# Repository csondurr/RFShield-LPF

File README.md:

# RFShield LPF

<p align="center">
  <strong>Python-assisted, PCB-aware 108–500 MHz / 50 Ω seventh-order RF low-pass filter design.</strong>
</p>

## Türkçe proje özeti

**RFShield LPF**, 50 Ω RF sinyal zincirlerinde **108 MHz ile 500 MHz** arasındaki işaretleri düşük kayıpla geçirmek ve daha yüksek frekans bileşenlerini bastırmak amacıyla geliştirilmiş, iki katmanlı, yedinci dereceden bir alçak geçiren filtre PCB projesidir. Tasarım; ayrık L/C değer optimizasyonu, parasitik etkileri içeren PCB-farkındalıklı analitik model, 50 Ω mikroşerit sentezi, Monte Carlo tolerans analizi, KiCad dosya üretimi, DRC doğrulaması ve üretim çıktılarının hazırlanması aşamalarını kapsar.

Bu çalışma bir **mühendislik prototipi** olarak yayımlanmaktadır. Analitik sonuçlar ve KiCad doğrulaması güçlü bir tasarım temeli sağlar; ancak fiziksel üretim sonrası VNA ölçümü, tam dalga elektromanyetik analiz ve hedef RF güç seviyesinde doğrulama yapılmadan seri üretim, maksimum güç veya mevzuat uyumluluğu iddiasında bulunulmaz.

---

## 1. Repository integrity and revision status

The public product name is **RFShield LPF**. Some checked-in files still use the original internal engineering identifier `CEM_RF_LPF_500_FINAL` and the historical revision label `REV_B`. Those identifiers are retained here for traceability and do not change the intended product name.

### Important status distinction

The repository currently contains an earlier engineering snapshot whose checked-in [`drc_summary.json`](drc_summary.json) reports:

```text
20 DRC warnings
0 unconnected items
```

All 20 warnings are of the same class: `via_dangling`. They were generated because the RF-route stitching vias were connected to the bottom ground plane but did not yet have a continuous top-copper connection.

A later **REV_C** production run corrected this by adding continuous F.Cu ground guard rails that electrically join the via fence on both copper layers. That run completed with:

```text
Found 0 violations
Found 0 unconnected items
```

Therefore:

- the RF topology and selected component values are the final intended design;
- the checked-in REV_B DRC report is historical evidence of the issue that was found;
- the corrected REV_C geometry is the manufacturing target;
- the current repository snapshot should not be treated as the final fabrication master until the corrected REV_C board source and its new DRC report are committed together.

This distinction is documented explicitly to avoid presenting a historical DRC report as if it were the final validated source.

---

## 2. Design objectives

| Parameter | Target |
|---|---:|
| Intended passband | 108–500 MHz |
| Reference impedance | 50 Ω |
| Filter class | Low-pass |
| Filter order | 7 |
| Network form | Symmetrical series-L / shunt-C ladder |
| PCB layer count | 2 |
| Nominal finished thickness | 1.60 mm |
| Nominal copper thickness | 35 µm |
| Nominal substrate | FR-4 |
| Nominal relative permittivity | 4.30 |
| Nominal loss tangent | 0.018 |
| Nominal dielectric height to ground | 1.53 mm |
| Input/output connector | 50 Ω SMA |
| Maximum analytical passband insertion-loss gate | 1.00 dB |
| Minimum analytical passband return-loss gate | 12.0 dB |
| Minimum analytical attenuation at 1 GHz | 25.0 dB |
| Minimum Monte Carlo pass gate | 95% |

The design is intended for use as a prototype output or interstage low-pass network in sub-500 MHz RF systems. Typical applications may include:

- harmonic suppression after a low-VHF/UHF RF stage;
- receiver front-end or laboratory filtering;
- SDR test chains;
- RF measurement fixtures;
- educational study of practical lumped-element filters and PCB parasitics.

It is not tied to one transmitter, one output power, one national emission mask, or one certified product.

---

## 3. Electrical topology

RFShield LPF uses a symmetrical seventh-order ladder:

```text
J1 ─ L1 ─●─ L3 ─●─ L5 ─●─ L7 ─ J2
         │      │      │
         C2     C4     C6
         │      │      │
        GND    GND    GND
```

Net sequence:

```text
RF_IN → L1 → N1 → L3 → N2 → L5 → N3 → L7 → RF_OUT
             │          │          │
             C2         C4         C6
             │          │          │
            GND        GND        GND
```

The symmetry reduces unnecessary input/output asymmetry and simplifies model verification.

### Selected values

| References | Quantity | Selected value | Tolerance used in analysis | Intended component family |
|---|---:|---:|---:|---|
| L1, L7 | 2 | 8.2 nH | ±5% | Coilcraft 0603HP high-Q RF inductor |
| L3, L5 | 2 | 15 nH | ±5% | Coilcraft 0603HP high-Q RF inductor |
| C2, C6 | 2 | 4.3 pF | ±0.1 pF | KYOCERA AVX 600S high-Q C0G/NP0 |
| C4 | 1 | 4.3 pF | ±0.1 pF | KYOCERA AVX 600S high-Q C0G/NP0 |
| J1, J2 | 2 | 50 Ω SMA | — | Amphenol RF 132134-10 family |

Intended example manufacturer part numbers:

| Function | Example MPN |
|---|---|
| 8.2 nH inductor | `0603HP-8N2XJRW` |
| 15 nH inductor | `0603HP-15NXJRW` |
| 4.3 pF capacitor | `600S4R3BT250XT4K` |
| SMA connector | `132134-10` |

Substitution must be based on RF characteristics, not only nominal value and package size. Inductor Q, self-resonant frequency, capacitor ESR/ESL, dielectric technology, pad geometry and connector launch geometry directly affect the upper passband and first stopband octave.

---

## 4. Why a seventh-order Chebyshev-style ladder was used

A higher-order ladder provides a steeper transition than a simple third- or fifth-order network while remaining practical with discrete components. The design began from a classical low-pass prototype approach and was then optimized using real candidate values and a PCB-aware model rather than relying on one ideal calculation followed by simple E-series rounding.

For an ideal low-pass prototype, series inductors and shunt capacitors can be scaled using:

```text
Lk = gk · Z0 / ωc
Ck = gk / (Z0 · ωc)
```

where:

- `gk` is the normalized prototype coefficient;
- `Z0` is the 50 Ω system impedance;
- `ωc` is the chosen angular cutoff frequency.

In a real PCB, the final values cannot be chosen from ideal equations alone because the transmission-line sections, component pads, vias, connector launches and finite component Q modify the response. RFShield LPF therefore performs a second-stage discrete optimization with these effects included.

---

## 5. Discrete component optimization

The engineering automation evaluates a finite candidate space rather than choosing the nearest values once.

Candidate sets:

```text
Outer inductors: 8.2, 9.1, 10, 11, 12 nH
Inner inductors: 15, 16, 18, 22, 24 nH
Outer capacitors: 4.3, 4.7, 5.1, 5.6, 6.2 pF
Center capacitor: 4.3, 4.7, 5.1, 5.6, 6.2 pF
```

Total combinations:

```text
5 × 5 × 5 × 5 = 625 candidate networks
```

Each candidate is evaluated from approximately 10 MHz to 2 GHz. The score penalizes:

- passband insertion loss;
- return loss falling below the acceptance gate;
- insufficient attenuation at 1 GHz;
- excessive passband ripple.

The best-performing candidate is selected automatically and the top 20 candidates are preserved in [`optimization_top20.json`](optimization_top20.json) for engineering traceability.

---

## 6. PCB-aware analytical model

The analysis cascades ABCD matrices for the individual network elements and converts the complete two-port network to S-parameters in a 50 Ω reference system.

### Series element matrix

```text
[ 1  Z ]
[ 0  1 ]
```

### Shunt element matrix

```text
[ 1  0 ]
[ Y  1 ]
```

### Transmission-line matrix

```text
[ cosh(γl)      Z0 sinh(γl) ]
[ sinh(γl)/Z0   cosh(γl)    ]
```

The complete matrix is the ordered product of connector, line, series-L, shunt-C and interconnect matrices.

### Included non-ideal effects

- frequency-dependent transmission-line electrical length;
- approximate conductor and dielectric loss;
- inductor finite Q;
- inductor parasitic capacitance estimated from self-resonant frequency;
- capacitor ESR;
- capacitor ESL;
- shunt-via inductance;
- dual-via ground return;
- finite shunt-stub length;
- connector series resistance and inductance;
- interstage microstrip lengths;
- real discrete candidate values.

### Effects not fully represented

- full 3D connector fields;
- solder fillets and assembly geometry;
- copper roughness tied to a specific laminate;
- vendor Touchstone models for every part;
- enclosure and cable coupling;
- radiation and higher-order mode effects;
- power-dependent heating and saturation;
- exact board-house etch and dielectric distributions.

The analytical model is therefore a strong design-screening tool, but it is not a substitute for full-wave EM simulation or calibrated measurement.

---

## 7. Predicted RF performance

The selected values produced the following PCB-aware analytical results:

| Metric | Predicted result |
|---|---:|
| Worst-case insertion loss in 108–500 MHz | **0.408 dB** |
| Worst-case return loss in 108–500 MHz | **23.370 dB** |
| Attenuation at 1 GHz | **30.837 dB** |
| S21 at 108 MHz | **−0.167 dB** |
| S21 at 500 MHz | **−0.409 dB** |
| S11 at 500 MHz | **−36.024 dB** |
| Predicted passband ripple | **0.242 dB** |

Machine-readable results are stored in [`design_summary.json`](design_summary.json).

### Interpretation

- The predicted passband loss is below the 1 dB engineering gate.
- The predicted return loss has significant margin above the 12 dB gate.
- The 1 GHz attenuation exceeds the 25 dB gate.
- These are model outputs, not measured VNA results.

No measured insertion-loss, return-loss, group-delay, power-handling or harmonic-compliance claim is made in this release.

---

## 8. Monte Carlo tolerance analysis

The selected design was evaluated with **400 deterministic, seeded Monte Carlo runs**.

Random seed:

```text
20260729
```

Tolerance assumptions:

- inductors: ±5%, represented as a normal distribution with the limit at approximately 3σ;
- capacitors: ±0.1 pF, represented in the same manner.

A run passes only when all three conditions are met:

```text
Worst passband IL ≤ 1.00 dB
Worst passband RL ≥ 12.0 dB
Attenuation at 1 GHz ≥ 25.0 dB
```

Reported model statistics:

| Metric | Result |
|---|---:|
| Monte Carlo runs | 400 |
| Passing runs | 100% |
| 95th-percentile passband IL | 0.415 dB |
| 5th-percentile passband RL | 22.161 dB |
| 5th-percentile attenuation at 1 GHz | 30.098 dB |

This result does not include every manufacturing variable. In particular, laminate Er variation, dielectric thickness tolerance, copper thickness, etch bias, connector spread and complete package-model uncertainty are not all randomized. The result must not be interpreted as a guaranteed production yield.

---

## 9. Stack-up and controlled impedance

Nominal two-layer stack-up:

```text
Top solder mask
F.Cu: 35 µm copper — RF components and signal routing
FR-4: Er = 4.30, tanδ = 0.018, nominal dielectric height = 1.53 mm
B.Cu: 35 µm copper — RF ground reference
Bottom solder mask
Nominal finished thickness: 1.60 mm
```

The microstrip width is solved with a Hammerstad-style quasi-static approximation.

| Parameter | Calculated value |
|---|---:|
| Target characteristic impedance | 50.000 Ω |
| Solved trace width | 2.9995 mm |
| Routed nominal trace width | 3.000 mm |
| Effective relative permittivity | 3.2683 |
| Calculated impedance at solved width | 50.000 Ω |

### Critical manufacturing warning

“1.6 mm FR-4” is not a complete controlled-impedance specification. Different fabricators may use different core/prepreg constructions, resin content, copper roughness and actual dielectric thickness.

Before ordering an impedance-controlled lot:

1. obtain the board house's actual stack-up;
2. confirm the dielectric height from F.Cu to B.Cu;
3. update Er, loss tangent and copper thickness;
4. recalculate the required trace width;
5. regenerate the PCB;
6. rerun DRC;
7. request an impedance coupon where available.

A 3.0 mm trace is appropriate only for the nominal stack-up used in this model. It is not a universal 50 Ω width.

---

## 10. PCB layout architecture

Nominal board dimensions:

```text
74 mm × 50 mm
```

### 10.1 RF signal path

The main RF route is kept linear and symmetrical. The nominal 50 Ω sections use a 3.0 mm microstrip width. Narrow necks are limited to locations where 0603 pad geometry requires a transition.

### 10.2 Ground reference

The bottom copper is intended as a continuous RF ground reference. A continuous reference plane minimizes loop area, lowers return-path inductance and makes the microstrip impedance definition physically meaningful.

### 10.3 Shunt-capacitor return paths

Each shunt capacitor requires a short and low-inductance path to ground. Dual local ground vias are used so that the shunt branches remain effective near the upper passband and into the stopband.

A long shared ground bus would add parasitic inductance, detune the ladder and reduce stopband attenuation. The layout avoids that architecture.

### 10.4 SMA launches

The SMA launches include nearby ground connections and stitching vias. The goal is to provide a short transition from the connector ground tabs to the bottom reference plane and to reduce connector-launch inductance.

The exact connector drawing must be checked against the purchased Amphenol part before fabrication. Similar-looking vertical SMA connectors are not footprint-compatible by default.

### 10.5 Via fence

The RF route is bordered by a ground via fence with an approximate 5 mm pitch. In the corrected REV_C geometry, front-copper guard rails connect the via fence on F.Cu while the bottom plane connects the same vias on B.Cu.

This change serves two purposes:

- it removes KiCad `via_dangling` warnings;
- it creates a physically continuous two-layer ground structure rather than a decorative set of vias connected on only one copper layer.

### 10.6 Local footprints

The project includes custom footprint sources:

- [`RF_0603.kicad_mod`](RF_0603.kicad_mod)
- [`SMA_AMPHENOL_132134_10.kicad_mod`](SMA_AMPHENOL_132134_10.kicad_mod)

The [`fp-lib-table`](fp-lib-table) expects a project-local library called `CUSTOM.pretty`. For a clean local checkout, place the two `.kicad_mod` files inside:

```text
CUSTOM.pretty/
```

so that the structure becomes:

```text
RFShield-LPF/
├── CEM_RF_LPF_500_FINAL.kicad_pcb
├── CEM_RF_LPF_500_FINAL.kicad_pro
├── fp-lib-table
└── CUSTOM.pretty/
    ├── RF_0603.kicad_mod
    └── SMA_AMPHENOL_132134_10.kicad_mod
```

The footprints embedded in the board allow the PCB to open, but restoring the intended local-library structure is recommended for future edits and reproducibility.

---

## 11. KiCad design files

| File | Purpose |
|---|---|
| [`CEM_RF_LPF_500_FINAL.kicad_pcb`](CEM_RF_LPF_500_FINAL.kicad_pcb) | Main PCB layout and embedded footprint geometry |
| [`CEM_RF_LPF_500_FINAL.kicad_pro`](CEM_RF_LPF_500_FINAL.kicad_pro) | KiCad project settings and net classes |
| [`CEM_RF_LPF_500_FINAL.kicad_prl`](CEM_RF_LPF_500_FINAL.kicad_prl) | KiCad local UI/session state; not required for fabrication |
| [`fp-lib-table`](fp-lib-table) | Project-local footprint library mapping |
| [`RF_0603.kicad_mod`](RF_0603.kicad_mod) | Custom RF 0603 land pattern |
| [`SMA_AMPHENOL_132134_10.kicad_mod`](SMA_AMPHENOL_132134_10.kicad_mod) | Custom SMA connector footprint |

The `.kicad_prl` file is machine/session specific and is normally excluded from a clean source repository. It is kept in the current snapshot only because it was included in the uploaded engineering package.

---

## 12. Reports and traceability files

| File | Description |
|---|---|
| [`design_summary.json`](design_summary.json) | Selected values, analytical metrics, Monte Carlo statistics and nominal stack-up |
| [`optimization_top20.json`](optimization_top20.json) | Ranked top 20 component combinations from the 625-candidate search |
| [`drc_report.json`](drc_report.json) | Historical KiCad 9.0.7 REV_B DRC report containing 20 `via_dangling` warnings |
| [`drc_summary.json`](drc_summary.json) | Compact summary of the historical REV_B DRC execution |

The report files are intended to make the design decision auditable instead of presenting only a final layout with no engineering history.

---

## 13. Opening the project

Recommended environment:

- Windows 10 or Windows 11;
- KiCad 9.0.7 or a compatible KiCad 9 release.

Procedure:

1. clone or download the repository;
2. create a `CUSTOM.pretty` folder in the repository root;
3. move the two `.kicad_mod` files into `CUSTOM.pretty`;
4. open `CEM_RF_LPF_500_FINAL.kicad_pro`;
5. open PCB Editor;
6. inspect the board stack-up, design rules, footprints and net classes;
7. refill or regenerate copper only when intentionally modifying the design;
8. run DRC locally before exporting any fabrication files.

Command-line DRC example:

```powershell
& "C:\Program Files\KiCad\9.0\bin\kicad-cli.exe" pcb drc `
  --output .\drc_report_new.json `
  --format json `
  --severity-all `
  --exit-code-violations `
  .\CEM_RF_LPF_500_FINAL.kicad_pcb
```

Do not assume that the historical checked-in report describes a modified local board. Always regenerate the report from the exact board revision intended for fabrication.

---

## 14. Intended automated production pipeline

The project was developed through a Python-driven engineering pipeline with the following sequence:

1. define RF and PCB requirements;
2. solve the nominal 50 Ω microstrip width;
3. validate board and component-placement constraints;
4. evaluate 625 discrete L/C candidate networks;
5. select the best candidate using PCB-aware metrics;
6. run 400 Monte Carlo tolerance trials;
7. enforce RF acceptance gates;
8. generate the KiCad PCB and project files;
9. generate custom project-local footprints;
10. generate analytical reports;
11. call KiCad CLI DRC;
12. require zero violations and zero unconnected items for release;
13. export Gerbers;
14. export PTH and NPTH drill files;
15. export drill maps;
16. export CSV component positions;
17. verify expected fabrication outputs;
18. create a production ZIP.

The current repository snapshot contains the generated design and reports, but it does not yet include the full Python automation source or the final REV_C fabrication archive. For complete reproducibility, those files should be versioned in a future repository cleanup.

---

## 15. Expected fabrication outputs

A complete release package should contain at minimum:

### Gerbers

- F.Cu;
- B.Cu;
- F.Paste;
- F.Silkscreen;
- B.Silkscreen;
- F.Mask;
- B.Mask;
- Edge.Cuts.

### Drill and assembly

- plated-through-hole Excellon file;
- non-plated-through-hole Excellon file;
- drill map;
- component position CSV;
- bill of materials;
- stack-up and impedance note;
- DRC report from the released source revision.

Gerber export example for KiCad 9:

```powershell
& "C:\Program Files\KiCad\9.0\bin\kicad-cli.exe" pcb export gerbers `
  --output .\fabrication\gerbers `
  --layers F.Cu,B.Cu,F.Paste,F.Silkscreen,B.Silkscreen,F.Mask,B.Mask,Edge.Cuts `
  .\CEM_RF_LPF_500_FINAL.kicad_pcb
```

Drill export example:

```powershell
& "C:\Program Files\KiCad\9.0\bin\kicad-cli.exe" pcb export drill `
  --output .\fabrication\drill `
  --format excellon `
  --excellon-units mm `
  --generate-map `
  --map-format pdf `
  --excellon-separate-th `
  .\CEM_RF_LPF_500_FINAL.kicad_pcb
```

---

## 16. Manufacturing checklist

Before ordering the PCB:

- use the corrected REV_C source, not the historical REV_B snapshot;
- confirm DRC is 0 violations and 0 unconnected items;
- verify every Gerber in an independent viewer;
- verify board dimensions and units;
- verify plated and non-plated drill separation;
- confirm the exact board-house stack-up;
- recalculate the 50 Ω width for that stack-up;
- confirm the exact SMA connector mechanical drawing;
- confirm 0603 component land patterns;
- verify solder-mask openings;
- verify via drill and annular-ring capability;
- verify copper-to-edge clearance;
- verify the BOM and current component availability;
- verify inductor Q and SRF for the full operating range;
- verify capacitor technology is C0G/NP0 or equivalent RF grade;
- order a small prototype quantity first;
- request impedance control or an impedance coupon where practical.

A DRC-clean board can still be electrically unsuitable at RF. Manufacturing review must include return-current paths, connector launches, trace impedance and parasitic behavior—not only geometric rule compliance.

---

## 17. Prototype assembly guidance

Recommended assembly sequence:

1. inspect the bare PCB for shorts, damaged mask and incorrect drill registration;
2. install the three shunt capacitors;
3. install the four series inductors;
4. install the SMA connectors with complete ground-tab soldering;
5. clean flux residues appropriate to the assembly process;
6. verify continuity from each ground pad and via to SMA ground;
7. verify there is no DC short from RF input to ground;
8. verify there is no DC short from RF output to ground;
9. inspect component alignment under magnification.

Because the component values are very small, excess solder, lifted parts, long solder fillets and incorrect component technology may noticeably shift the response.

---

## 18. VNA validation plan

Recommended first measurement:

1. warm up the VNA according to the instrument procedure;
2. use high-quality 50 Ω cables and minimize adapters;
3. perform SOLT calibration at the cable ends or use an appropriate fixture calibration;
4. sweep at least 10 MHz to 2 GHz;
5. record S11, S21, S12 and S22;
6. save Touchstone data;
7. compare measured S21 with the analytical response;
8. inspect passband loss, return loss, cutoff shift and first stopband resonance;
9. repeat on a second assembled PCB;
10. document the exact board stack-up and component lot.

Recommended plots:

- S21 magnitude from 10 MHz to 2 GHz;
- S11 and S22 magnitude;
- passband-only S21 zoom from 108 MHz to 500 MHz;
- group delay in the passband;
- measured-versus-modeled overlay.

Possible causes of model/measurement mismatch:

- actual Er or dielectric thickness differs from nominal;
- component Q/SRF differs from the simplified model;
- connector launch parasitics;
- incorrect or substitute components;
- via inductance and ground-return geometry;
- solder and pad parasitics;
- calibration-plane error;
- cable or adapter repeatability.

---

## 19. Power-path validation

Small-signal VNA data is not sufficient to establish a power rating.

For transmitter or PA use, perform a controlled power test with:

- a rated 50 Ω load;
- directional couplers;
- suitable attenuators;
- a spectrum analyzer or power meter;
- thermal monitoring;
- appropriate shielding and RF safety precautions.

Validate:

- insertion loss at operating power;
- harmonic attenuation;
- inductor current and temperature;
- capacitor RF voltage stress;
- connector heating;
- solder-joint heating;
- response drift with temperature;
- behavior under load mismatch.

No maximum RF power is claimed by this repository.

---

## 20. Known limitations

- The checked-in source snapshot is the historical REV_B package, not the corrected REV_C manufacturing master.
- The checked-in DRC report contains 20 `via_dangling` warnings.
- The final REV_C 0/0 DRC report is not yet committed.
- Physical VNA data is not yet published.
- Full-wave 2.5D/3D EM results are not yet published.
- The nominal FR-4 stack-up is not tied to one fabricator.
- The model uses engineering approximations for line and component parasitics.
- Vendor S-parameter files are not included.
- Maximum RF power has not been established.
- Thermal behavior has not been measured.
- Regulatory harmonic-emission compliance is not claimed.
- The filter has not been co-simulated with a specific PA output impedance.
- The current root-level footprint placement should be reorganized into `CUSTOM.pretty`.
- The complete automation source and production ZIP are not included in the present repository snapshot.

---

## 21. Engineering roadmap

Planned next steps:

- commit the corrected REV_C KiCad source;
- replace the historical DRC report with a revision-matched 0/0 report while preserving REV_B history in a separate folder;
- restore `CUSTOM.pretty` directory structure;
- add the full Python automation source;
- add BOM and component lifecycle information;
- add generated Gerbers and drills as a tagged release asset;
- perform ADS Momentum, Sonnet, CST or equivalent EM extraction;
- import vendor S-parameter models;
- manufacture at least two prototypes;
- publish calibrated VNA Touchstone files;
- correlate analytical and measured responses;
- evaluate power handling and thermal rise;
- optimize against a specific board-house stack-up;
- add automated repository validation and release checks.

---

## 22. Safety and regulatory notice

RF hardware can cause interference, equipment damage, burns and unlawful emissions when used incorrectly. The builder and operator are responsible for:

- complying with local spectrum regulations;
- using legal frequencies and power levels;
- using properly rated loads, cables, attenuators and instruments;
- preventing exposure to hazardous RF levels;
- ensuring that a transmitter system satisfies applicable harmonic and spurious-emission requirements.

This repository is provided as an engineering and educational project, not as regulatory certification.

---

## 23. Project metadata

| Field | Value |
|---|---|
| Public name | RFShield LPF |
| Internal engineering identifier | CEM_RF_LPF_500_FINAL |
| Intended final hardware revision | REV_C |
| Frequency range | 108–500 MHz |
| System impedance | 50 Ω |
| Filter order | 7 |
| PCB layers | 2 |
| Primary EDA tool | KiCad 9.0.7 |
| Analysis environment | Python, NumPy-based numerical model |
| Author | Cem Sondur |
| Project year | 2026 |

---

## 24. License and use

Unless a separate license file is added, all project files remain copyright of **Cem Sondur**.

No warranty is provided. Anyone fabricating, modifying or operating the design is responsible for independent review, measurement, safety and regulatory compliance.

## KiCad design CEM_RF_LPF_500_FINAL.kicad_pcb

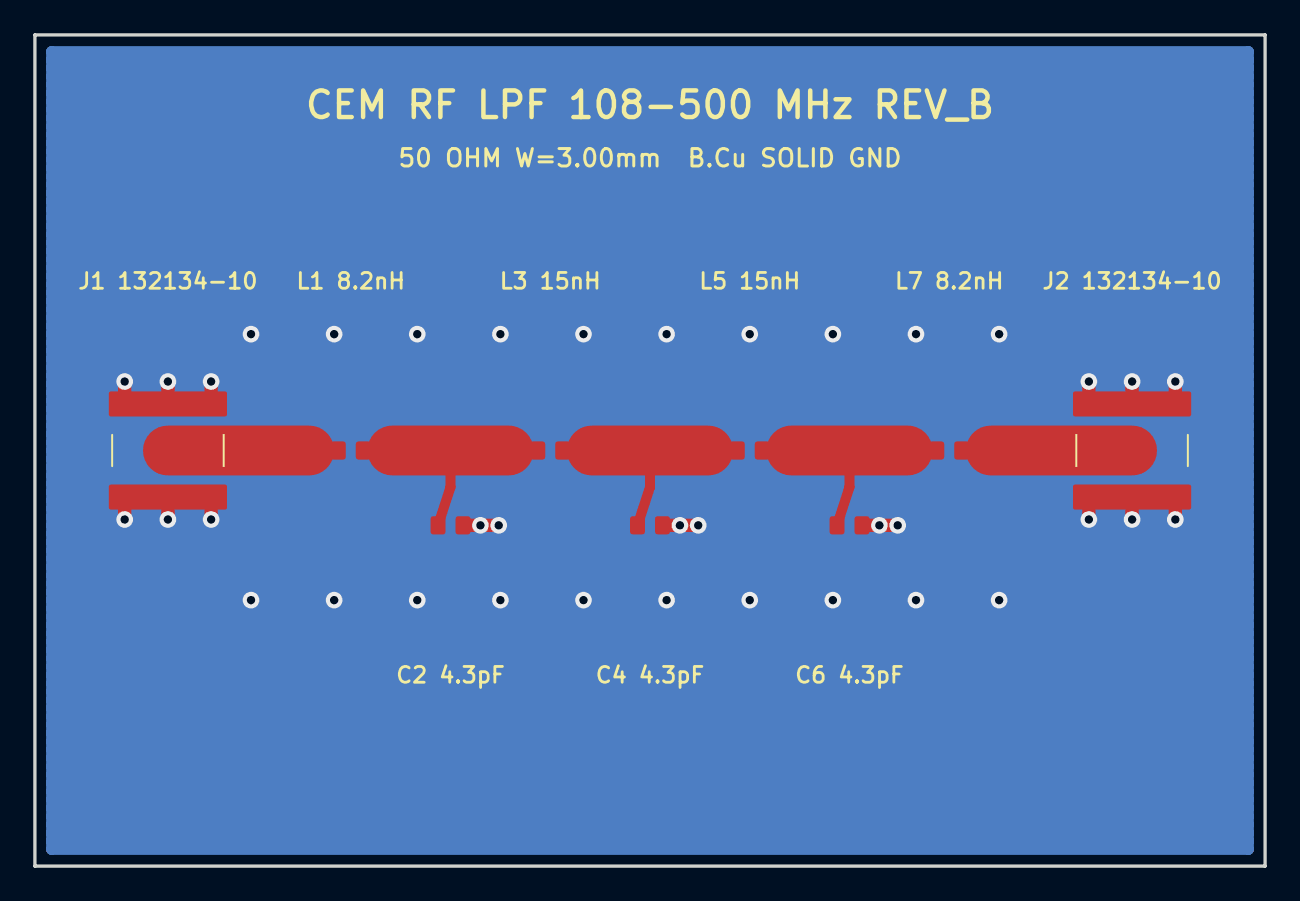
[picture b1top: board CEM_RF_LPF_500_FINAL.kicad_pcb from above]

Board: 2 copper layers, 74.0 x 50.0 mm, 9 parts (0 on the bottom side), 6 nets.

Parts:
C2, C4, C6: 4.3pF; RF_0603
J1, J2: 132134-10; SMA_AMPHENOL_132134_10
L1, L7: 8.2nH; RF_0603
L3, L5: 15nH; RF_0603

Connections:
GND: C2.2, C4.2, C6.2, J1.2 (GND), J2.2 (GND)
N1: C2.1, L1.2, L3.1
N2: C4.1, L3.2, L5.1
N3: C6.1, L5.2, L7.1
RF_IN: J1.1 (RF), L1.1
RF_OUT: J2.1 (RF), L7.2
